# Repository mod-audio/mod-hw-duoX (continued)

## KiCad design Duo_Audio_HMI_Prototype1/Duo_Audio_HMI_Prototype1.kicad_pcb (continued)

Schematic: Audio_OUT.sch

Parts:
CAP14: 100nF; SM0603
CAS17, CAS18: 3.3uF; CAP_RAD_5MM
CAS19, CAS20: 2.2nF; SM0603
D4, D5: 1N4007; DO-214AC(SMA)
J1, J2: JACK_P10_TRS_6P; JACK-NMJ6HCD2_1
K1, K2: IM03TS
Q5, Q6: BS870; SOT23
R73, R74: 10k; SM0603
R75, R76: 33k; SM0603
RAS43, RAS44: 150R; RES_PTH_6MM
RAS45, RAS46: 300R; RES_PTH_6MM
RAS47, RAS48: 1k; RES_PTH_6MM
RAS49, RAS50: 100R; RES_PTH_6MM
UA13: LM4562; SO8E

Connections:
+5VA: D4.2 (K), D5.2 (K), K1.1, K2.1, R75.2, R76.2; also elsewhere on the board
AGND: CAP14.1, CAS19.1, CAS20.1, J1.3, J1.5, J2.3, J2.5, Q5.2 (S), Q6.2 (S), RAS47.2, RAS48.2, UA13.4 (V-); also elsewhere on the board
AMPOUT_L_IN: RAS44.2; also elsewhere on the board
AMPOUT_L_OUT: CAS20.2, RAS50.1; also elsewhere on the board
AMPOUT_R_IN: RAS43.2; also elsewhere on the board
AMPOUT_R_OUT: CAS19.2, RAS49.1; also elsewhere on the board
BYPASS_L: D5.1 (A), K2.8, Q6.3 (D), R76.1
BYPASS_L_EN: R74.2; also elsewhere on the board
BYPASS_R: D4.1 (A), K1.8, Q5.3 (D), R75.1
BYPASS_R_EN: R73.2; also elsewhere on the board
IN_L: K2.7 (R); also elsewhere on the board
IN_R: K1.7 (R); also elsewhere on the board
unnamed: RAS44.1, UA13.5 (+)
unnamed: CAS18.1, RAS46.1, UA13.7
unnamed: RAS46.2, UA13.6 (-)
unnamed: RAS43.1, UA13.3 (+)
unnamed: CAS17.2, RAS47.1, RAS49.2
unnamed: J1.1, K1.6 (C)
unnamed: J2.1, K2.6 (C)
unnamed: CAS18.2, RAS48.1, RAS50.2
unnamed: Q5.1 (G), R73.1
unnamed: Q6.1 (G), R74.1
unnamed: RAS45.2, UA13.2 (-)
unnamed: CAS17.1, RAS45.1, UA13.1
OUT_L: K2.5 (T); also elsewhere on the board
OUT_R: K1.5 (T); also elsewhere on the board
VCC_AMP_AUDIO: CAP14.2, UA13.8 (V+); also elsewhere on the board

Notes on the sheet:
OUTPUT RIGHT
OUTPUT LEFT

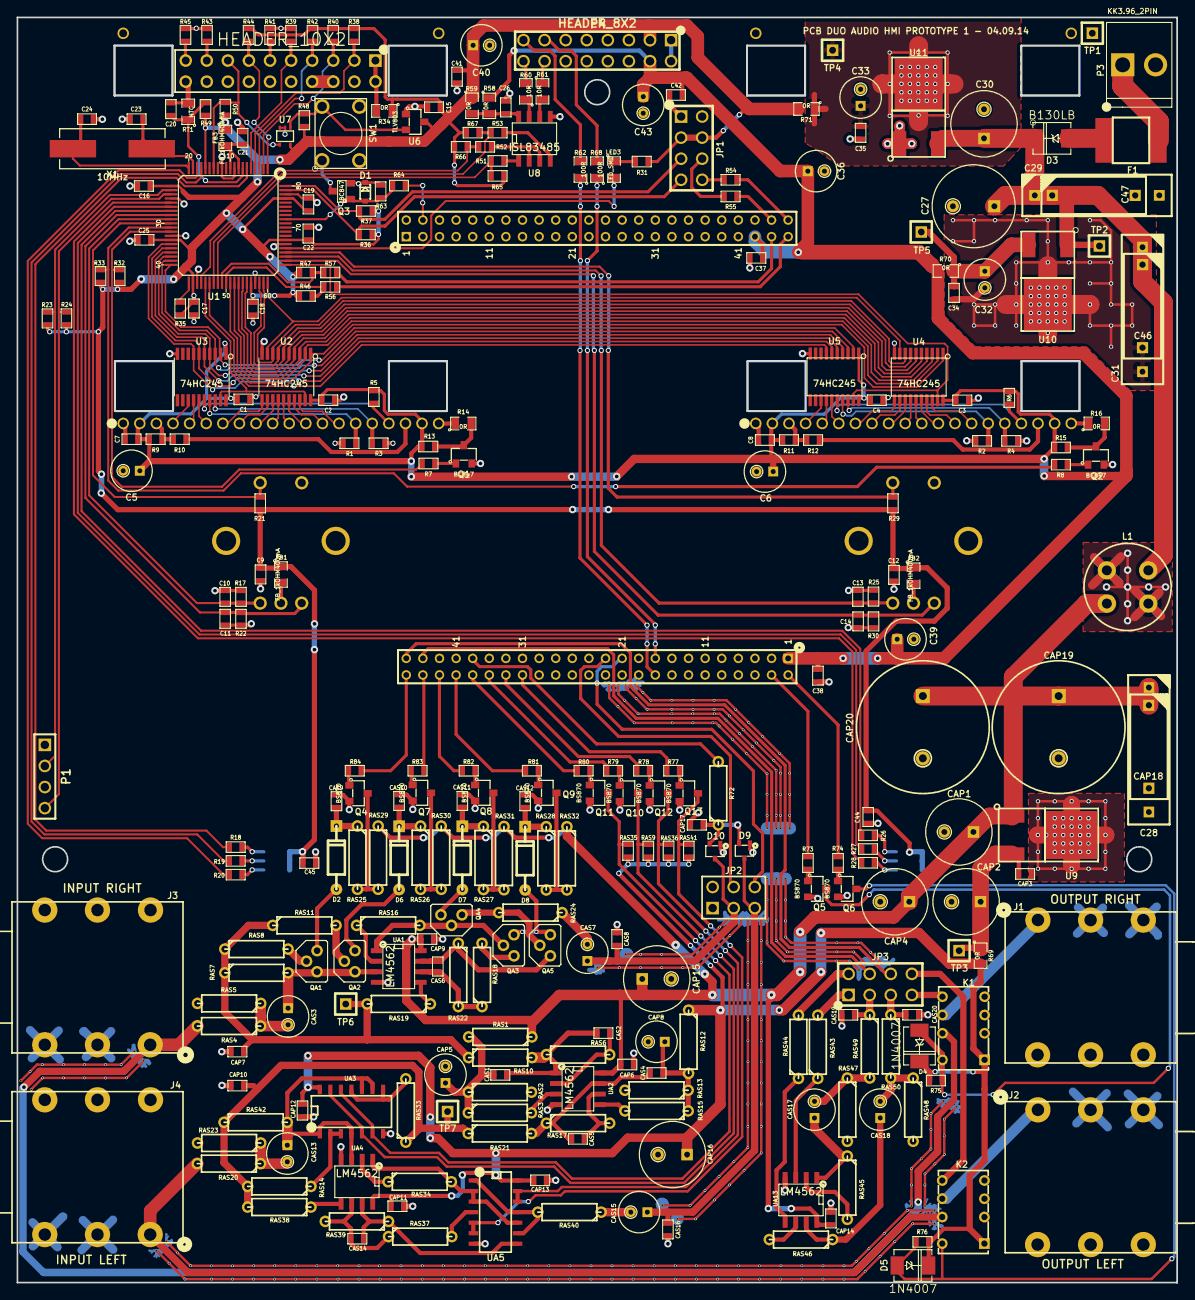
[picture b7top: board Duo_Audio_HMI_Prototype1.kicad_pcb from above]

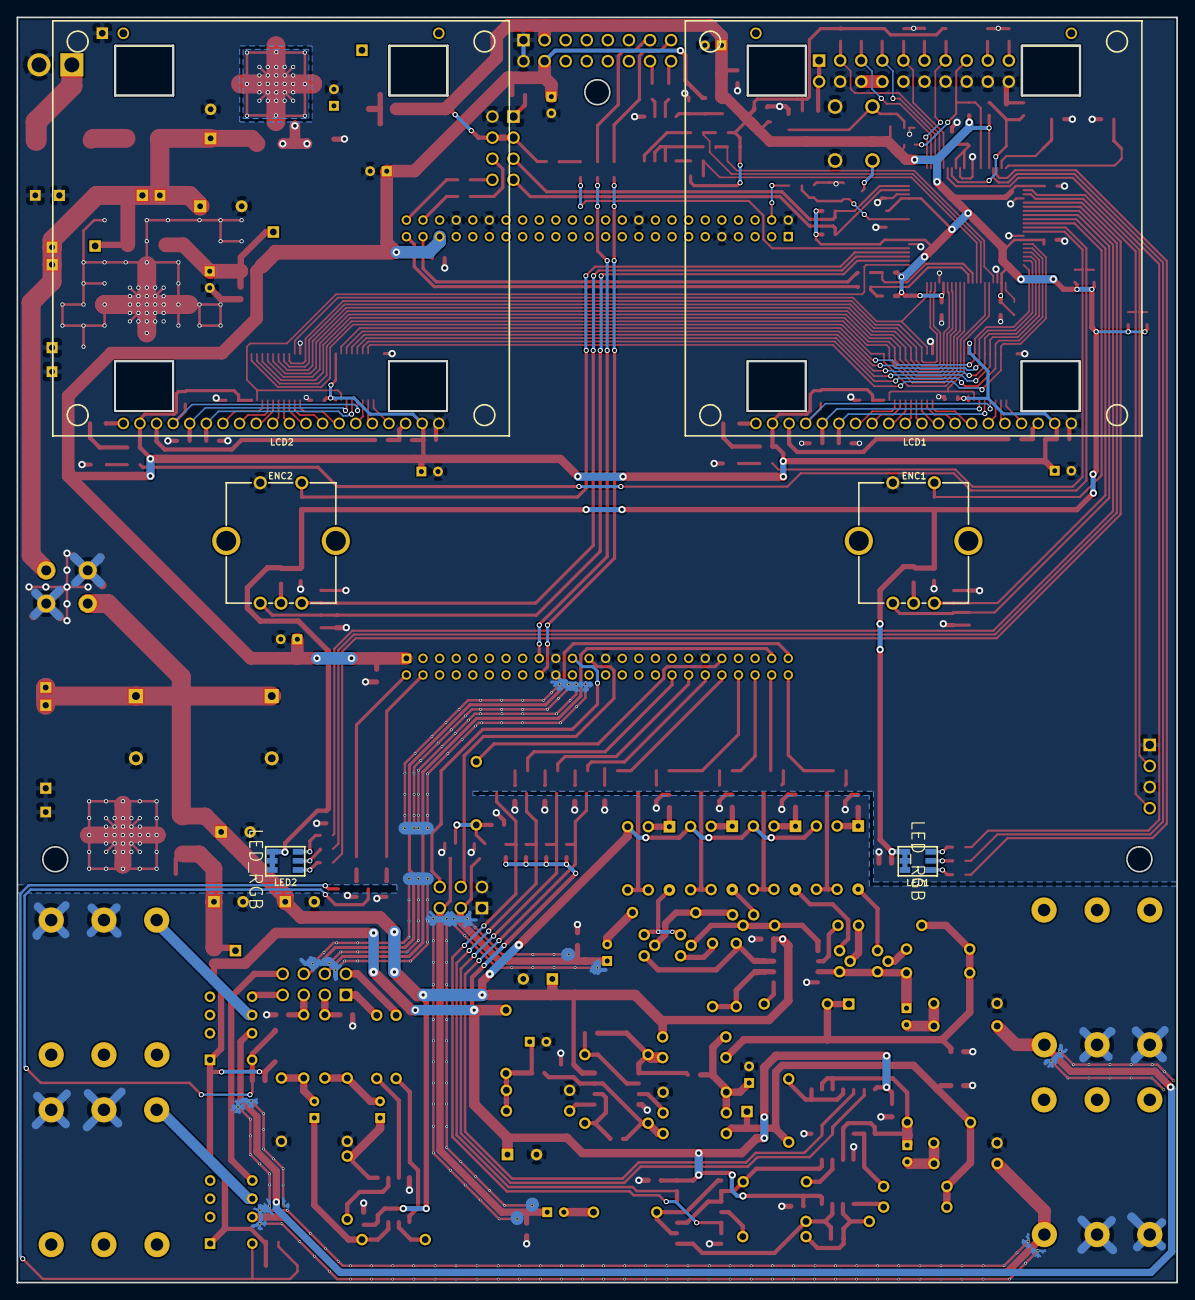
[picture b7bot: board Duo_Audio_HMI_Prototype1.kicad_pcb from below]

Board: 2 copper layers, 139.7 x 152.4 mm, 336 parts (6 on the bottom side), 233 nets.

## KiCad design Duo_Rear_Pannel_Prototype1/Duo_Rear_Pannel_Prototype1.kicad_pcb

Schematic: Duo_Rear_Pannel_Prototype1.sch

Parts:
C1, C5, C10, C11, C12, C13, C14: 100nF_X7R; SM0603
C2: 100nF_MF; CAP_FILM_12.6X4.5_L10
C3, C4, C16: 100uF; CAP_RAD_5MM
C15: 100nF_MKP; CAP_FILM_18X5_L15
CN1, CN2: CONN_PANNEL_2X2; CONN_PANNEL
D3, D4: MMSZ5242B; SOD123_
D5, D6: 1N4148; SOD323
FB2, FB3: FB_150OHM800mA; SM0805
J1: RJ45_CHAIN; RJ45_TFN2_88_1
J2: JACK_3P; PJ-002B
P1: USB_A; USB_A_73725
P2, P3: MIDI_CONN; CON_MIDI_SDS-50J
P4: HEADER_8X2; pin_array_8x2
P5: KK3.96_2PIN
P7: HEADER_2X2; PIN_ARRAY_2X2
Q1, Q2: BS870; SOT23
R1: 120R; SM0805
R7, R8, R15, R16: 1k; SM0603
R12, R13, R14: 220R; SM0805
R18: 280R; SM0603
U3: 6N137; SMD_8

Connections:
+3.3V: C14.2, P4.4, R18.2
+5V: C12.2, C13.1, P4.3, R7.2, R12.2, R15.2, R16.2, U3.8 (VCC)
+9V: C2.2, C4.1, C5.1, C15.2, C16.1, J1.1, J1.2, J2.1, P5.2 (PM)
CHAIN_A: D4.2, D5.2 (K), J1.3, J1.4, P4.13, R1.1
CHAIN_B: D3.2, J1.5, J1.6, P4.15, R1.2, R8.2
DGND: C1.1, C2.1, C3.2, C4.2, C5.2, C10.2, C11.2, C12.1, C13.2, C14.1, C15.1, C16.2, D3.1, D4.1, FB2.1, J1.7, J1.8, J1.9 (SHIELD), J1.10 (SHIELD), J2.2, J2.3, P1.4 (GND), P2.2, P4.1, P4.2, P5.1, P7.3, Q1.2 (S), Q2.2 (S), R8.1, U3.5 (GND)
MIDI_IN_UART: P4.16, R18.1, U3.6 (VO)
MIDI_OUT_UART: P4.14, Q2.1 (G)
unnamed: D5.1 (A), R7.1
unnamed: Q1.3 (D), R14.2, R15.1
unnamed: P2.4, R12.1
unnamed: C10.1, P2.6, P2.7
unnamed: Q1.1 (G), Q2.3 (D), R16.1
unnamed: P2.5, R14.1
unnamed: P1.2 (D-), P7.2
unnamed: C3.1, FB3.2
unnamed: C1.2, FB3.1, P1.1 (Vbus), P7.1
unnamed: P1.3 (D+), P7.4
unnamed: FB2.2, P1.5 (Shield1), P1.6 (Shield2), P1.7 (Shield3), P1.8 (Shield4)
unnamed: C11.1, P3.6, P3.7
unnamed: D6.2 (K), R13.2, U3.2 (ANODE)
unnamed: D6.1 (A), P3.5, U3.3 (CATODE)
unnamed: P3.4, R13.1

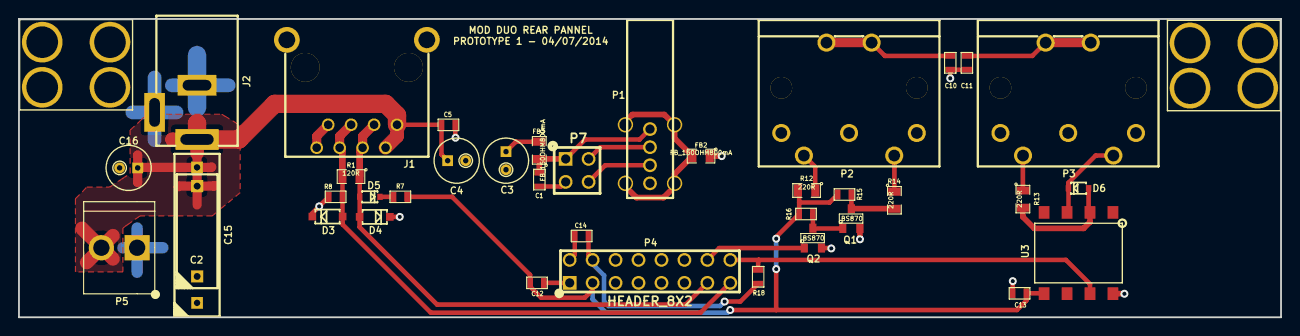
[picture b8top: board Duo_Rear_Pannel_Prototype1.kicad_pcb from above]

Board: 2 copper layers, 139.7 x 33.0 mm, 40 parts (0 on the bottom side), 23 nets.

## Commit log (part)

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2015-12-07 bottom-board,pcb: more headphone connections
2015-12-07 bottom-board,pcb: new positions for JFETs switches
2015-12-08 bottom-board,sch: removing extra codec I/Os connections
2015-12-08 bottom-board,pcb: more control chain tracks done
2015-12-08 bottom-board,sch: connecting usb signals to cpu
2015-12-08 bottom-board,pcb: all digital tracks done
2015-12-08 bottom-board,pcb: all analog tracks done
2015-12-08 bottom-board: unifing grounds and applying filled zones
2015-12-08 bottom-board,pcb: adding some vias to +5VA heatsink
2015-12-08 bottom-board,pcb: power tracks removed
2015-12-08 bottom-board,pcb: most of GND connected
2015-12-08 bottom-board,pcb: more GND connections
2015-12-08 bottom-board,pcb: 3.3V tracks done
2015-12-08 bottom-board,pcb: 12V digital connected
2015-12-08 bottom-board,pcb: layout finished
2015-12-10 bottom-board: gerber files updated
2015-12-10 bottom-board: gerber file updated (2layers)
2015-12-23 sch,bottom-board: added 100nF cap to twi memory IC
2015-12-23 sch,bottom-board: adjusting usb device circuit
2016-01-06 bottom-board,sch: replacing 24AA02E64T-I/OT by AT24CS08-STUM
2016-01-06 bottom-board,pcb: importing netlist
2016-01-07 bottom-board,pcb: applying new changes to layout
2016-01-07 bottom-board,pcb: copper area filled
2016-01-07 bottom-board,pcb: PM leds pull up resistor removed
2016-01-07 bottom-board,pcb: gerber updated
2016-01-08 bottom-board,pcb: adding mod log + gerber updated
2016-01-08 top-board,sch: inverting LEDs peak meter logic
2016-01-08 top-board,pcb: gerber updated
2016-02-02 bottom-board,pcb: added 'no component' tag
2016-02-02 top-board,pcb: fix extra tracks
2016-02-05 bottom-board,pcb: plotting more gerber files and renaming others
2016-02-05 top-board,pcb: plotting more gerber files and renaming others
2016-02-05 bottom-board,pcb: added footprint position file
2016-02-05 bottom-board: change CA19 and CA20 only for KS production
2016-03-12 bottom-board,sch: add pull up resistor to shutdown pin
2016-03-12 bottom-board: netlist updated
2016-03-12 bottom-board,sch: connecting grounds and updating netlist
2016-03-12 bottom-board,pcb: updating to last netlist
2016-03-12 top-board: add notes to pcb and BOM
2016-04-26 changed website address
2016-06-20 move FEL button a little inside
2016-06-20 bottom-board: update gerber and fabrication files
2016-11-29 bottom,sch: fix broken opamp connections
2016-11-29 bottom,pcb: remove headphone shutdown circuit
2016-11-29 bottom,pcb: protect grounding pads from pour area (fix #40)
2016-11-29 bottom,pcb: update revision date
2016-11-30 bottom-board: update BOM
2016-11-30 bottom-board: update position file
2017-01-21 bottom,sch: remove sdcard header pins
2017-04-07 bottom,sch: small improvements to usb device circuit
2017-05-15 bottom,sch: add 3.3V regulator for the codec
2017-05-15 bottom,sch: replace RJ45 connector to plastic version
2017-05-17 bottom,sch: add open jumper between 3.3V and 3.3VA (tests purpose)
2017-05-19 bottom,sch: add missing footprints
2017-05-22 bottom,sch: add test points
2017-05-24 bottom,sch: swap opamp's and update netlist
2017-05-24 bottom,sch: split input bias in 2 to facilitate the layout
2017-05-24 bottom,pcb: most codec interface signals connected
2017-05-25 bottom,sch: swap output op amp
2017-05-25 bottom,pcb: gain control signals connected
2017-05-25 bottom,pcb: many power tracks connected
2017-05-26 bottom,pcb: control chain components re-placed
2017-05-26 bottom,pcb: many signals tracks connected
2017-06-06 bottom,sch: control chain leds are now controlled by DE/RE I/Os
2017-06-07 bottom,pcb: +12VA and audio output tracks connected
2017-06-07 bottom, pcb: headphone and bypass control signals connected
2017-06-09 bottom,pcb: all signals tracks connected (hopefully)
2017-06-09 bottom,sch: connect GNDA and GNDD
2017-06-12 bottom,pcb: all GND tracks connected
2017-06-12 bottom,sch: update BOM
2017-06-12 bottom,pcb: update gerber and fabrication files
    leiton prototype ordered
2017-08-28 bottom,sch: add series resistors to codec signals
2017-08-28 bottom,sch: add capacitors to RJ45 leds to improve brightness
2017-08-28 bottom,sch: add missing annotation and remove sdcard signals from coreboard
2017-08-29 bottom,sch: set L1 footprint
2018-01-16 replace LPF components
2018-05-07 add new files
2018-05-09 sketch route of the components
2018-05-09 Routing buttons & mux
2018-05-11 check & cleanup
2018-05-17 Fixed ERC & DRC tests
2018-05-18 added MAX4781
2018-05-22 finishing layout
2018-05-29 libraries conflit
2018-06-29 add bottom board rescue library
2018-06-29 fix kicad_pcb file to work with kicad v4
2018-07-13 bottom,sch: add CV in/out circuit, update headphone circuit
2018-07-18 bottom,sch: add negative power rail
2018-07-19 bottom,sch: update audio input circuit
    - replace JFETs by analog switches
    - using dual power rails
    - new gain values
2018-07-23 bottom,sch: copy RJ-45 connector to control chain sheet
2018-07-24 bottom,sch: initial spdif circuit
2018-07-24 bottom,sch: move hmi connector to power sheet
2018-07-26 bottom,sch: update coreboard pinout [wip]
2018-07-27 bottom,sch: fix parts after updating to kicad 5
2018-07-30 bottom,sch: MPN updated on power sheet
2018-07-31 bottom,sch: MPN updated on codec sheet
2018-07-31 bottom,sch: MPN updated on audio inputs sheet
2018-08-01 bottom,sch: MPN updated on audio headphones sheet
2018-08-01 bottom,sch: MPN updated on control voltage sheet
2018-08-01 bottom,sch: MPN updated on midi sheet
2018-08-02 bottom,sch: MPN updated on spdif sheet
2018-08-02 bottom,sch: replace midi opto
2018-08-02 bottom,sch: define footprint for coreboard pins
2018-08-02 add new footprints to the local library
2018-08-03 bottom,sch: rename MPN1 to MPN
2018-08-03 bottom: update netlist and BOM
2018-08-24 Updated BOM
    Changed encoder part number - new model has 24 mechanical detents
2018-08-24 bottom,sch: swap op amp units
2018-08-24 lib: fix NMJ6HCD2 pins name
2018-08-24 lib: rename MJ-3536N footprint pinout
2018-08-24 bottom,pcb: initial work on codec circuit
2018-08-24 bottom,pcb: initial work on control chain circuit
2018-08-24 bottom,pcb: initial work on power rails circuit
2018-08-24 lib: add SDS-50J footprint
2018-08-24 bottom,sch: annotate schematic symbols again
2018-08-24 bottom,sch: swap usb devices I/Os on protection diodes
2018-08-24 bottom,sch: fix few footprints name
2018-08-27 bottom,pcb: initial work on cv in circuit
2018-08-28 bottom,pcb: (re)placement of the audio circutry
2018-08-28 bottom,pcb: work on spdif circuit
2018-08-29 bottom,pcb: work on power supply footprints
2018-08-30 lib: add footprints
2018-08-30 bottom,pcb: initial placement of coreboard footprints
2018-08-30 bottom,pcb: [wip] coreboard IOs connections
2018-09-03 bottom: replace coreboard connector
2018-09-03 bottom: coreboard/codec connections
2018-09-05 bottom,pcb: layout finished
2018-09-05 bottom,pcb: remove stand-off
2018-09-05 bottom,pcb: update gerber and output files
2018-09-06 bottom,sch: add alternative parts for the linear regulators
2018-09-11 lib: add missing footprints to the local library
2018-09-13 bottom,pcb: better placement of footprint values texts
2018-09-20 bottom,pcb: improve footprint silkscreens position
2018-09-20 bottom: small improvement on usb dev signals
2018-09-21 bottom: fix footprints U20 and U6
2018-10-01 bottom,sch: many fixes and addition of test points
2018-10-01 bottom,sch: replace 3.3V regulator
2018-10-01 bottom,sch: add pull dowm to cv in bias switch
2018-10-02 bottom,sch: fix jfet footprints
2018-10-02 bottom,sch: add logo
2018-10-05 bottom,sch: add more test points
2018-10-05 bottom,sch: swap hp signals
2018-10-05 bottom,pcb: many connections done
2018-10-09 bottom,sch: change gain control pull up to pull down
2018-10-09 bottom,pcb: spdif connected
2018-10-09 bottom: update gerber files
2018-11-06 bottom,sch: update library cache
2018-11-07 bottom,pcb: increase Fab labels size
2018-12-13 bottom,sch: revert midi opto part number; expose serial debug in the midi out conn
2018-12-13 bottom,sch: fix default state of input gains (pull-up); change J109 -> J110
2018-12-13 bottom,sch: fix swapped channels codec (dac)
2018-12-13 bottom,sch: update netlist and bom
2018-12-13 bottom,sch: remove cli uart rx pull-up
2018-12-13 bottom,pcb: apply sch changes to pcb layout
2018-12-13 bottom,pcb: update output files (gerber+position)
2018-12-14 bottom: add MCLK codec connection for future use
2018-12-21 update files to kicad 5
2018-12-21 change headphones caps to 100uF (same footprint); bom updated
2019-03-28 Changed README
2019-04-05 flipped HMI power connector + and GND to match the HMI
2019-04-08 removed cv out bias, this would not work when the receiving device grounded to earth
2019-04-15 added the final topboard to the design
2019-04-15 removed not needed fabrication outputs
2019-04-16 Changed bottomboard silkscreen
2019-04-29 added pick and place files for the coreboard adapter
2019-10-16 fix bottomboard SPDIF + fix DRC errors
2019-11-18 fix SPDIFF layout
2019-11-18 add 10V regulator, also, made CV input 0 - 10V compatible
2019-11-18 allow a fake nagative bias at -5 volts
2019-11-18 add pullups to EXP mode flags for proper detection of overcurrent
2019-11-18 increase filtering caps next to delay, less noise on low freqs
2019-11-18 add pullup resistor for proper CV input detection
2019-11-18 remove adapter files
2019-11-18 add adapter as submodule
2019-12-06 added holes for new adapter + add jack detection
2019-12-09 move PSU filtering caps more towards top connectors
2019-12-19 move DC filter + add fabrication files
2020-01-09 remove 10V regulator for the CV out opamp (stupid me)
2020-01-13 move DC jack up to 3mm pacing with the board + add reverse current protection diodes for EXP mode
2020-02-19 added schottky diodes exp mode + updated fabrication files
2020-02-27 add usb dev spike cap
2020-02-27 remove old fabrication files
2020-03-04 change cv switch + update pcb
2020-03-04 add HMI pulldown resistor
2020-03-05 move PSU caps up a bit
2020-03-05 update fabrication files
2020-03-05 remove tmp fabrication files
2020-05-14 update adapter stud MPN
2020-05-14 update PSU filtering caps MPN
2020-05-14 remove switch drive, as its not needed
2020-05-14 move CA20 out of the way for the CPU adapter
2020-05-15 change U10 MPN
2020-05-15 reroute CV output switches
2020-05-15 add bottomboard fabrication files
2020-05-15 make R19 and debug headers virtual components and update fabrication files
2020-05-15 update controller board
2020-05-15 update RK3399 adapter fabrication files
2020-05-20 finalize fabrication files
2020-11-19 fix schematic being out of sync
2020-11-19 change bias voltages to 5V, isolate input GND connections
2020-11-19 change revision
2020-11-25 change PnP files
2021-10-28 add docs + change pwr schematic
2021-10-29 match power circuit with the dwarf
2021-10-29 improve codec filtering
2021-10-29 redo headphone output
2021-10-29 improve CV range and bias
2021-10-29 change CC connector
2021-11-01 add firefly carier board docs
2021-11-01 remove coreboard adapter submodule
2021-11-02 sync .sch and .pcb
2021-11-02 route new output circuit
2021-11-02 use 10V for output detect pins
2021-11-02 first half of star ground
2021-11-03 route codec to new SoM
2021-11-03 fix DAC symbol + GND
2021-11-03 finalize routing and polygons
2021-11-03 update silkscreen
2021-11-10 update connector placement
2021-11-11 update all MPN's to match the Dwarf
2021-11-17 move connectors
2022-01-21 fix U1 ()10V regulator footprint
2022-01-21 connect 5VD with 5V_SYS (otherwise ff-rk3399 doesnt boot)
2022-01-21 use 1V8 logic level for CS4265 codec
2022-01-21 change U21 (EXP supply) MPN, due to unavailabilaty again
2022-01-21 separate input bias per channel (reduces crosstalk)
2022-01-21 make sure all GNDD connections are pressent
2022-01-25 change HMI connector type
2022-01-25 fix prev commit
2022-01-26 fix 3d package related kicad6 issues
2022-01-27 buffer bias per input
2022-04-05 change HMI connector, LEDS, Buck convertor and rotate the encoders
2022-04-22 cleanup and controller bottom overlay update
